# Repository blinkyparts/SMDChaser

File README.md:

# SMD_Lauflicht

The running light is achieved by a circuit of a clockgenerator NE555 (U1) and two shift registers TI4017 (U2, U3). The NE555 uses the clock signal to shift one bit through both shift registers. At the end the circuit is reset and the cycle starts anew. The outputs of U2 controls the 20 LEDs (D1-D20). Since the TI4017 only has 10 outputs, one output controls  two LEDs. U3 controls one transistor each (Q1, Q2) using two outputs, which alternately pull D1-D10 or D11-D20 to GND. This process repeats itself.

- Status: **Complete**
- Difficulty: **4/5**

### Parts List

| Pos.|References   	| Value       		| Quantity    | 
| --- | --------------- | --------------------- | ----------- |
|1    | C1, C2      	| 100n F       		| 2           | 
|2    |	C           	| 1µ F         		| 1           |
|3    | R1-R20      	| 82 Ohm      		| 20          |
|4    | R21, R22    	| 100k Ohm    		| 2           |
|5    | R23, R24    	| 1k Ohm      		| 2           |
|6    | D1-D20      	| LED          		| 20          |
|7    | U1          	| NE555       		| 1           |
|8    | U2, U3      	| TI4017      		| 2           |
|9    | SW1         	| SW_DPDT_x2  		| 1           |
|10   | Q1, Q2     	| BC850        		| 2           |
|12   | Battery Holder	| Battery_Holder	| 1           |
|13   | Battery     	| CR2032      		| 1           |
|14   | PCB         	| SMD-Lauflicht		| 1           |

### Manual
You can find the manual and pictures of every step in the manual folder.

## PCB Layout
The PCB-Layout can be found on Github: tbd

## Video
A video of the running PCB can be found here: [YouTube](https://youtu.be/Xx-zP-Ia8_w)

## Copyright and Authorship
- PCB-Layout: [CC-BY-SA 4.0](https://creativecommons.org/licenses/by-sa/4.0/) - [Taxxizz](https://twitter.com/Taxxizz)
- Manual (TeX): [LPPL](https://www.latex-project.org/lppl.txt) - [Marei Peischl](https://peitex.de)
- Manual (pdf): [CC-BY-SA 4.0](https://creativecommons.org/licenses/by-sa/4.0/) - [Binary Kitchen e.V.](https://www.binary-kitchen.de)

### Buy Soldering Kits
If you want to buy the parts and PCB for a soldering kit you can find everything here: [shop.blinkyparts.com - Running Light](https://shop.blinkyparts.com/en/SMD-running-light-Soldering-kit-for-the-proper-learning-of-soldering-SMD-components/blink233142)

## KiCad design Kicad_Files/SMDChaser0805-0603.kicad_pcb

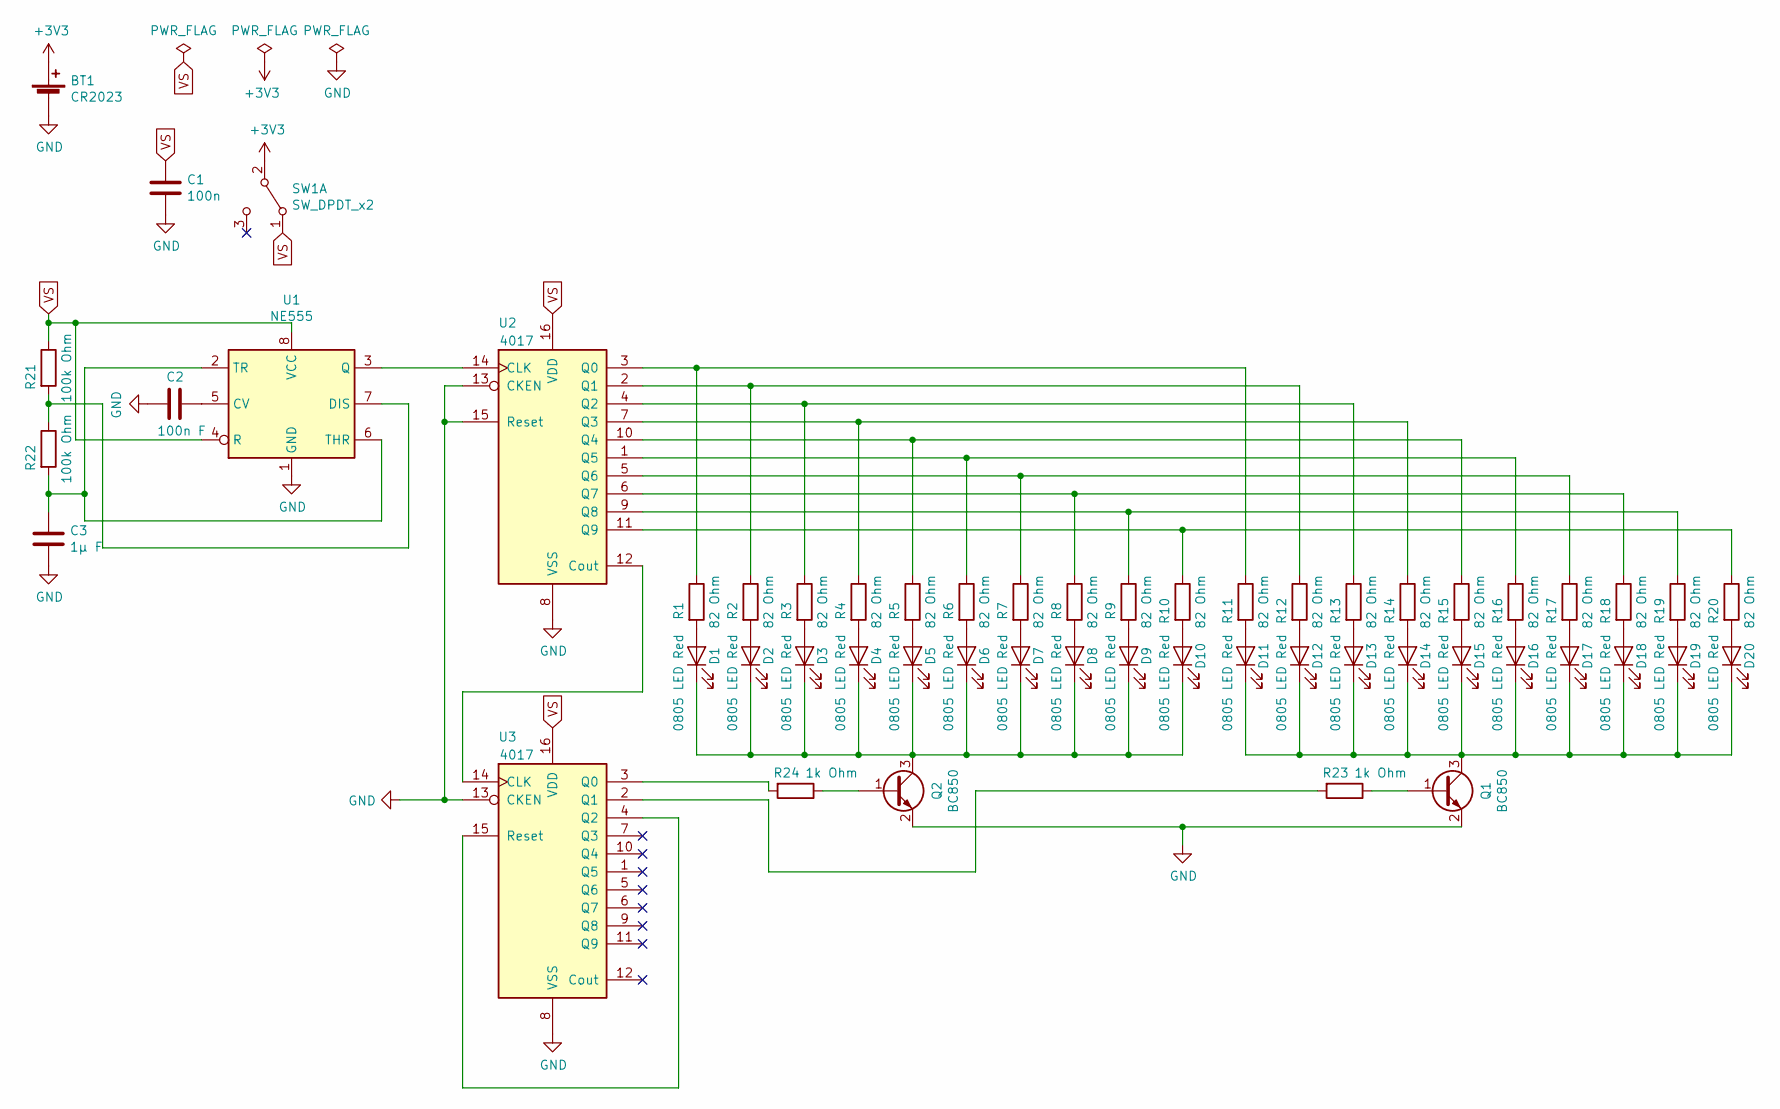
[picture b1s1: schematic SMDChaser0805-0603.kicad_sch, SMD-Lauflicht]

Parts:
BT1: CR2023; BatteryHolder_Keystone_1060_1x2032
C1: 100n; C_0805_2012Metric_Pad1.15x1.40mm_HandSolder
C2: 100n F; C_0805_2012Metric_Pad1.15x1.40mm_HandSolder
C3: 1µ F; C_0805_2012Metric_Pad1.15x1.40mm_HandSolder
D1, D2, D3, D4, D5, D6, D7, D8, D9, D10, D11, D12, D13, D14, D15, D16, D17, D18, D19, D20: 0805 LED Red; LED_0805_2012Metric_Pad1.15x1.40mm_HandSolder_simple_drawing
Q1, Q2: BC850; SOT-23
R1, R2, R3, R4, R5, R6, R7, R8, R9, R10, R11, R12, R13, R14, R15, R16, R17, R18, R19, R20: 82 Ohm; R_0603_1608Metric_Pad1.05x0.95mm_HandSolder
R21, R22: 100k Ohm; R_0805_2012Metric_Pad1.15x1.40mm_HandSolder
R23, R24: 1k Ohm; R_0603_1608Metric_Pad1.05x0.95mm_HandSolder
SW1: SW_DPDT_x2; smd_switch_slide
U1: NE555; SOIC-8_3.9x4.9mm_P1.27mm
U2, U3: 4017; SOP-16_4.4x10.4mm_P1.27mm_simple_drawing

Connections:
+3V3: BT1.1 (+), SW1.2 (B)
GND: BT1.2 (-), C1.1, C2.1, C3.1, Q1.2 (E), Q2.2 (E), U1.1 (GND), U2.8 (VSS), U2.13 (CKEN), U2.15 (Reset), U3.8 (VSS), U3.13 (CKEN)
unnamed: C2.2, U1.5 (CV)
unnamed: C3.2, R22.2, U1.2 (TR), U1.6 (THR)
unnamed: D1.1 (K), D2.1 (K), D3.1 (K), D4.1 (K), D5.1 (K), D6.1 (K), D7.1 (K), D8.1 (K), D9.1 (K), D10.1 (K), Q2.3 (C)
unnamed: D1.2 (A), R1.2
unnamed: D2.2 (A), R2.2
unnamed: D3.2 (A), R3.2
unnamed: D4.2 (A), R4.2
unnamed: D5.2 (A), R5.2
unnamed: D6.2 (A), R6.2
unnamed: D7.2 (A), R7.2
unnamed: D8.2 (A), R8.2
unnamed: D9.2 (A), R9.2
unnamed: D10.2 (A), R10.2
unnamed: D11.1 (K), D12.1 (K), D13.1 (K), D14.1 (K), D15.1 (K), D16.1 (K), D17.1 (K), D18.1 (K), D19.1 (K), D20.1 (K), Q1.3 (C)
unnamed: D11.2 (A), R11.2
unnamed: D12.2 (A), R12.2
unnamed: D13.2 (A), R13.2
unnamed: D14.2 (A), R14.2
unnamed: D15.2 (A), R15.2
unnamed: D16.2 (A), R16.2
unnamed: D17.2 (A), R17.2
unnamed: D18.2 (A), R18.2
unnamed: D19.2 (A), R19.2
unnamed: D20.2 (A), R20.2
unnamed: Q1.1 (B), R23.1
unnamed: Q2.1 (B), R24.1
unnamed: R1.1, R11.1, U2.3 (Q0)
unnamed: R10.1, R20.1, U2.11 (Q9)
unnamed: R2.1, R12.1, U2.2 (Q1)
unnamed: R3.1, R13.1, U2.4 (Q2)
unnamed: R4.1, R14.1, U2.7 (Q3)
unnamed: R5.1, R15.1, U2.10 (Q4)
unnamed: R6.1, R16.1, U2.1 (Q5)
unnamed: R7.1, R17.1, U2.5 (Q6)
unnamed: R8.1, R18.1, U2.6 (Q7)
unnamed: R9.1, R19.1, U2.9 (Q8)
unnamed: R21.2, R22.1, U1.7 (DIS)
unnamed: R23.2, U3.2 (Q1)
unnamed: R24.2, U3.3 (Q0)
unnamed: U1.3 (Q), U2.14 (CLK)
unnamed: U2.12 (Cout), U3.14 (CLK)
unnamed: U3.4 (Q2), U3.15 (Reset)
VS: C1.2, R21.1, SW1.1 (A), U1.4 (R), U1.8 (VCC), U2.16 (VDD), U3.16 (VDD)

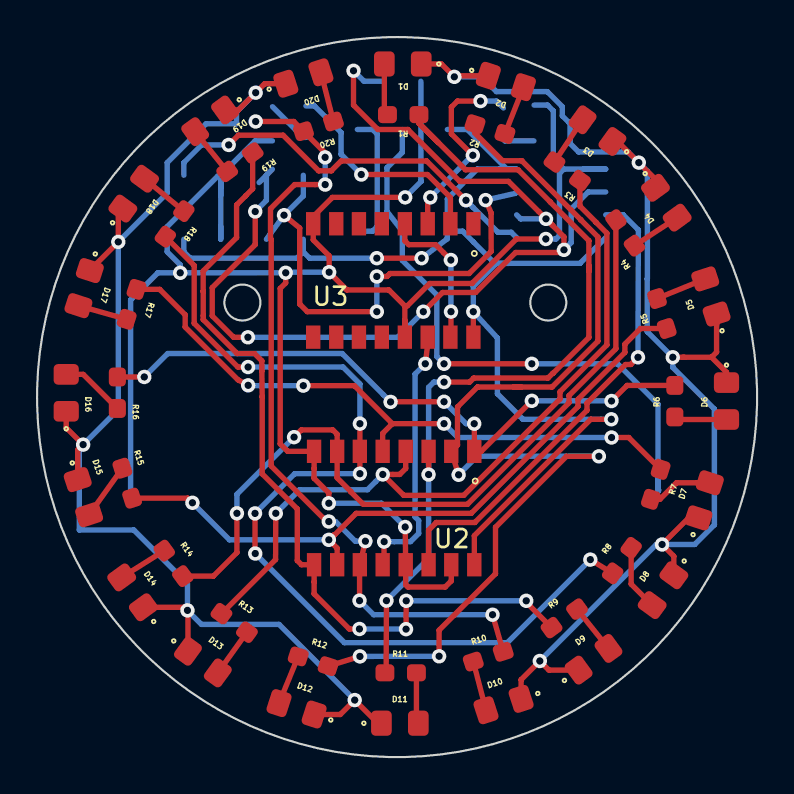
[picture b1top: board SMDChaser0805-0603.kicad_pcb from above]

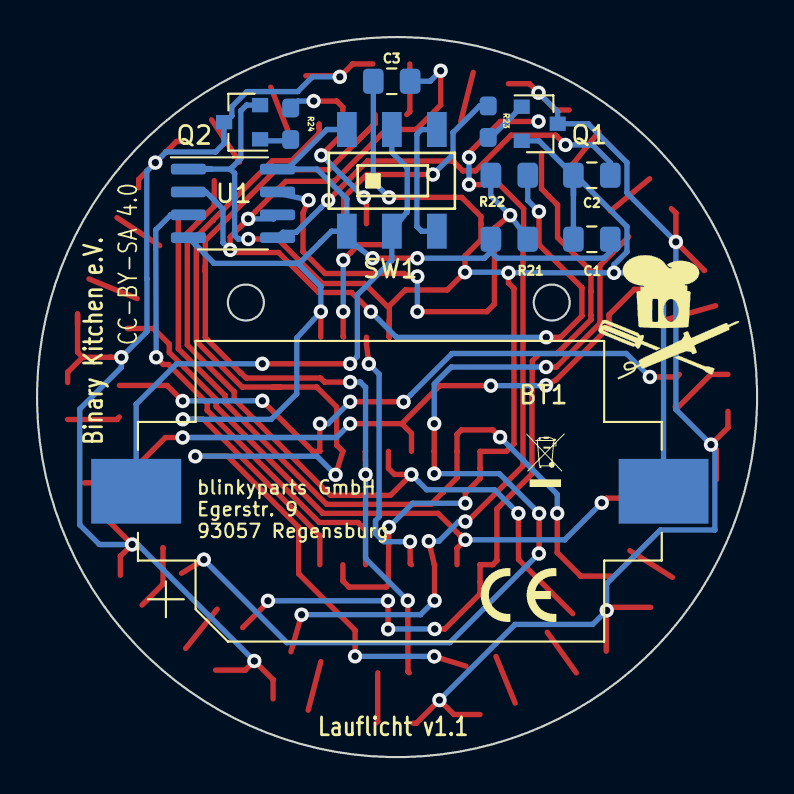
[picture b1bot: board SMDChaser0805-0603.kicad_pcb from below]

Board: 2 copper layers, 40.0 x 40.0 mm, 56 parts (14 on the bottom side), 45 nets.

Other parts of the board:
ce-symbol_mask_3mm: G***; ce-icon_3mm
weee-symbol_mask_3mm: G***; weee-icon_3mm

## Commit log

2022-11-29 exchanged cr2032 battery holder
2022-11-29 created gerber-files
2025-04-09 moved some files and added v1.1
